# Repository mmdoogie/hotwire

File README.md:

# hotwire
Small PWM controller for power control of a hot wire foam cutter

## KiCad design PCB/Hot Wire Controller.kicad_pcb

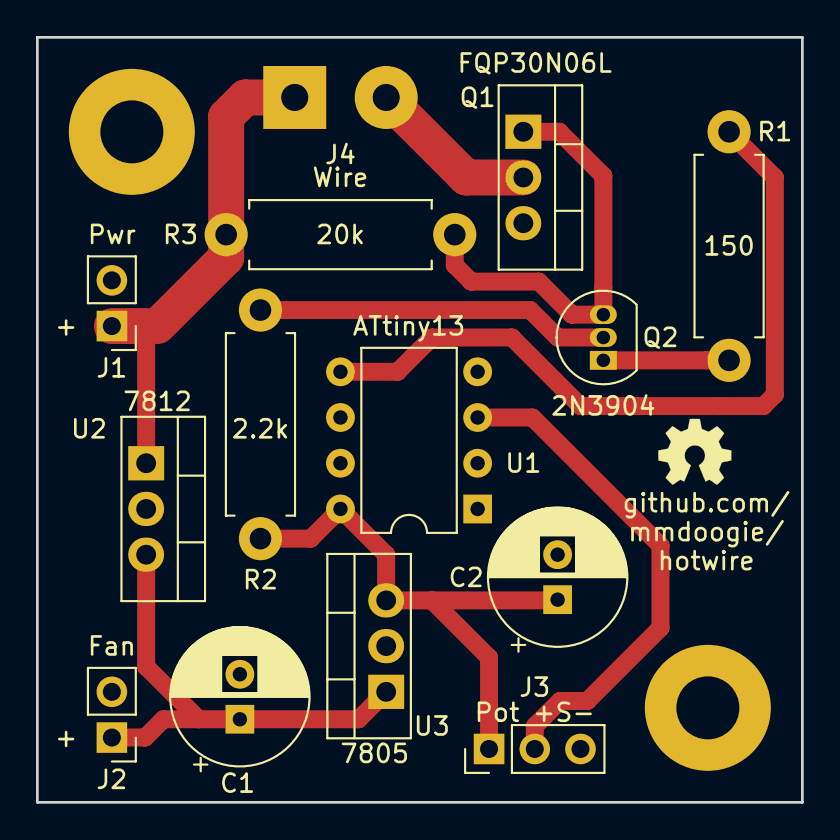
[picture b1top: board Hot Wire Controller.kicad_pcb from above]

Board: 2 copper layers, 42.5 x 42.5 mm, 16 parts (0 on the bottom side), 10 nets.

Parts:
C1, C2: 100u; CP_Radial_D7.5mm_P2.50mm
J1: Power; PinHeader_1x02_P2.54mm_Vertical
J2: Fan; PinHeader_1x02_P2.54mm_Vertical
J3: Pot; PinHeader_1x03_P2.54mm_Vertical
J4: Wire; SolderWirePad_1x02_P5.08mm_Drill1.5mm
MH1, MH2: Fan; MountingHole_3.5mm_Pad
Q1: FQP30N06L; TO-220-3_Vertical
Q2: 2N3904; TO-92_Inline
R1: 150; R_Axial_DIN0411_L9.9mm_D3.6mm_P12.70mm_Horizontal
R2: 2.2k; R_Axial_DIN0411_L9.9mm_D3.6mm_P12.70mm_Horizontal
R3: 20k; R_Axial_DIN0411_L9.9mm_D3.6mm_P12.70mm_Horizontal
U1: ATtiny13-20PU; DIP-8_W7.62mm
U2: L7812; TO-220-3_Vertical
U3: L7805; TO-220-3_Vertical

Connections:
+5V: C2.1, J3.1, R2.1, U1.8, U3.3
+12V: C1.1, J2.1, U2.3, U3.1
+VDC: J1.1, J4.1, R3.1, U2.1
GND: C1.2, C2.2, J1.2, J2.2, J3.3, MH1.1, MH2.1, Q1.3, U1.4, U2.2, U3.2
unnamed: J3.2, U1.3
unnamed: J4.2, Q1.2
unnamed: Q1.1, Q2.3, R3.2
unnamed: Q2.1, R1.1
unnamed: Q2.2, R2.2
unnamed: R1.2, U1.5

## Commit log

2021-09-25 Project structure and initial ignores
2021-09-25 Initial PCB revision
